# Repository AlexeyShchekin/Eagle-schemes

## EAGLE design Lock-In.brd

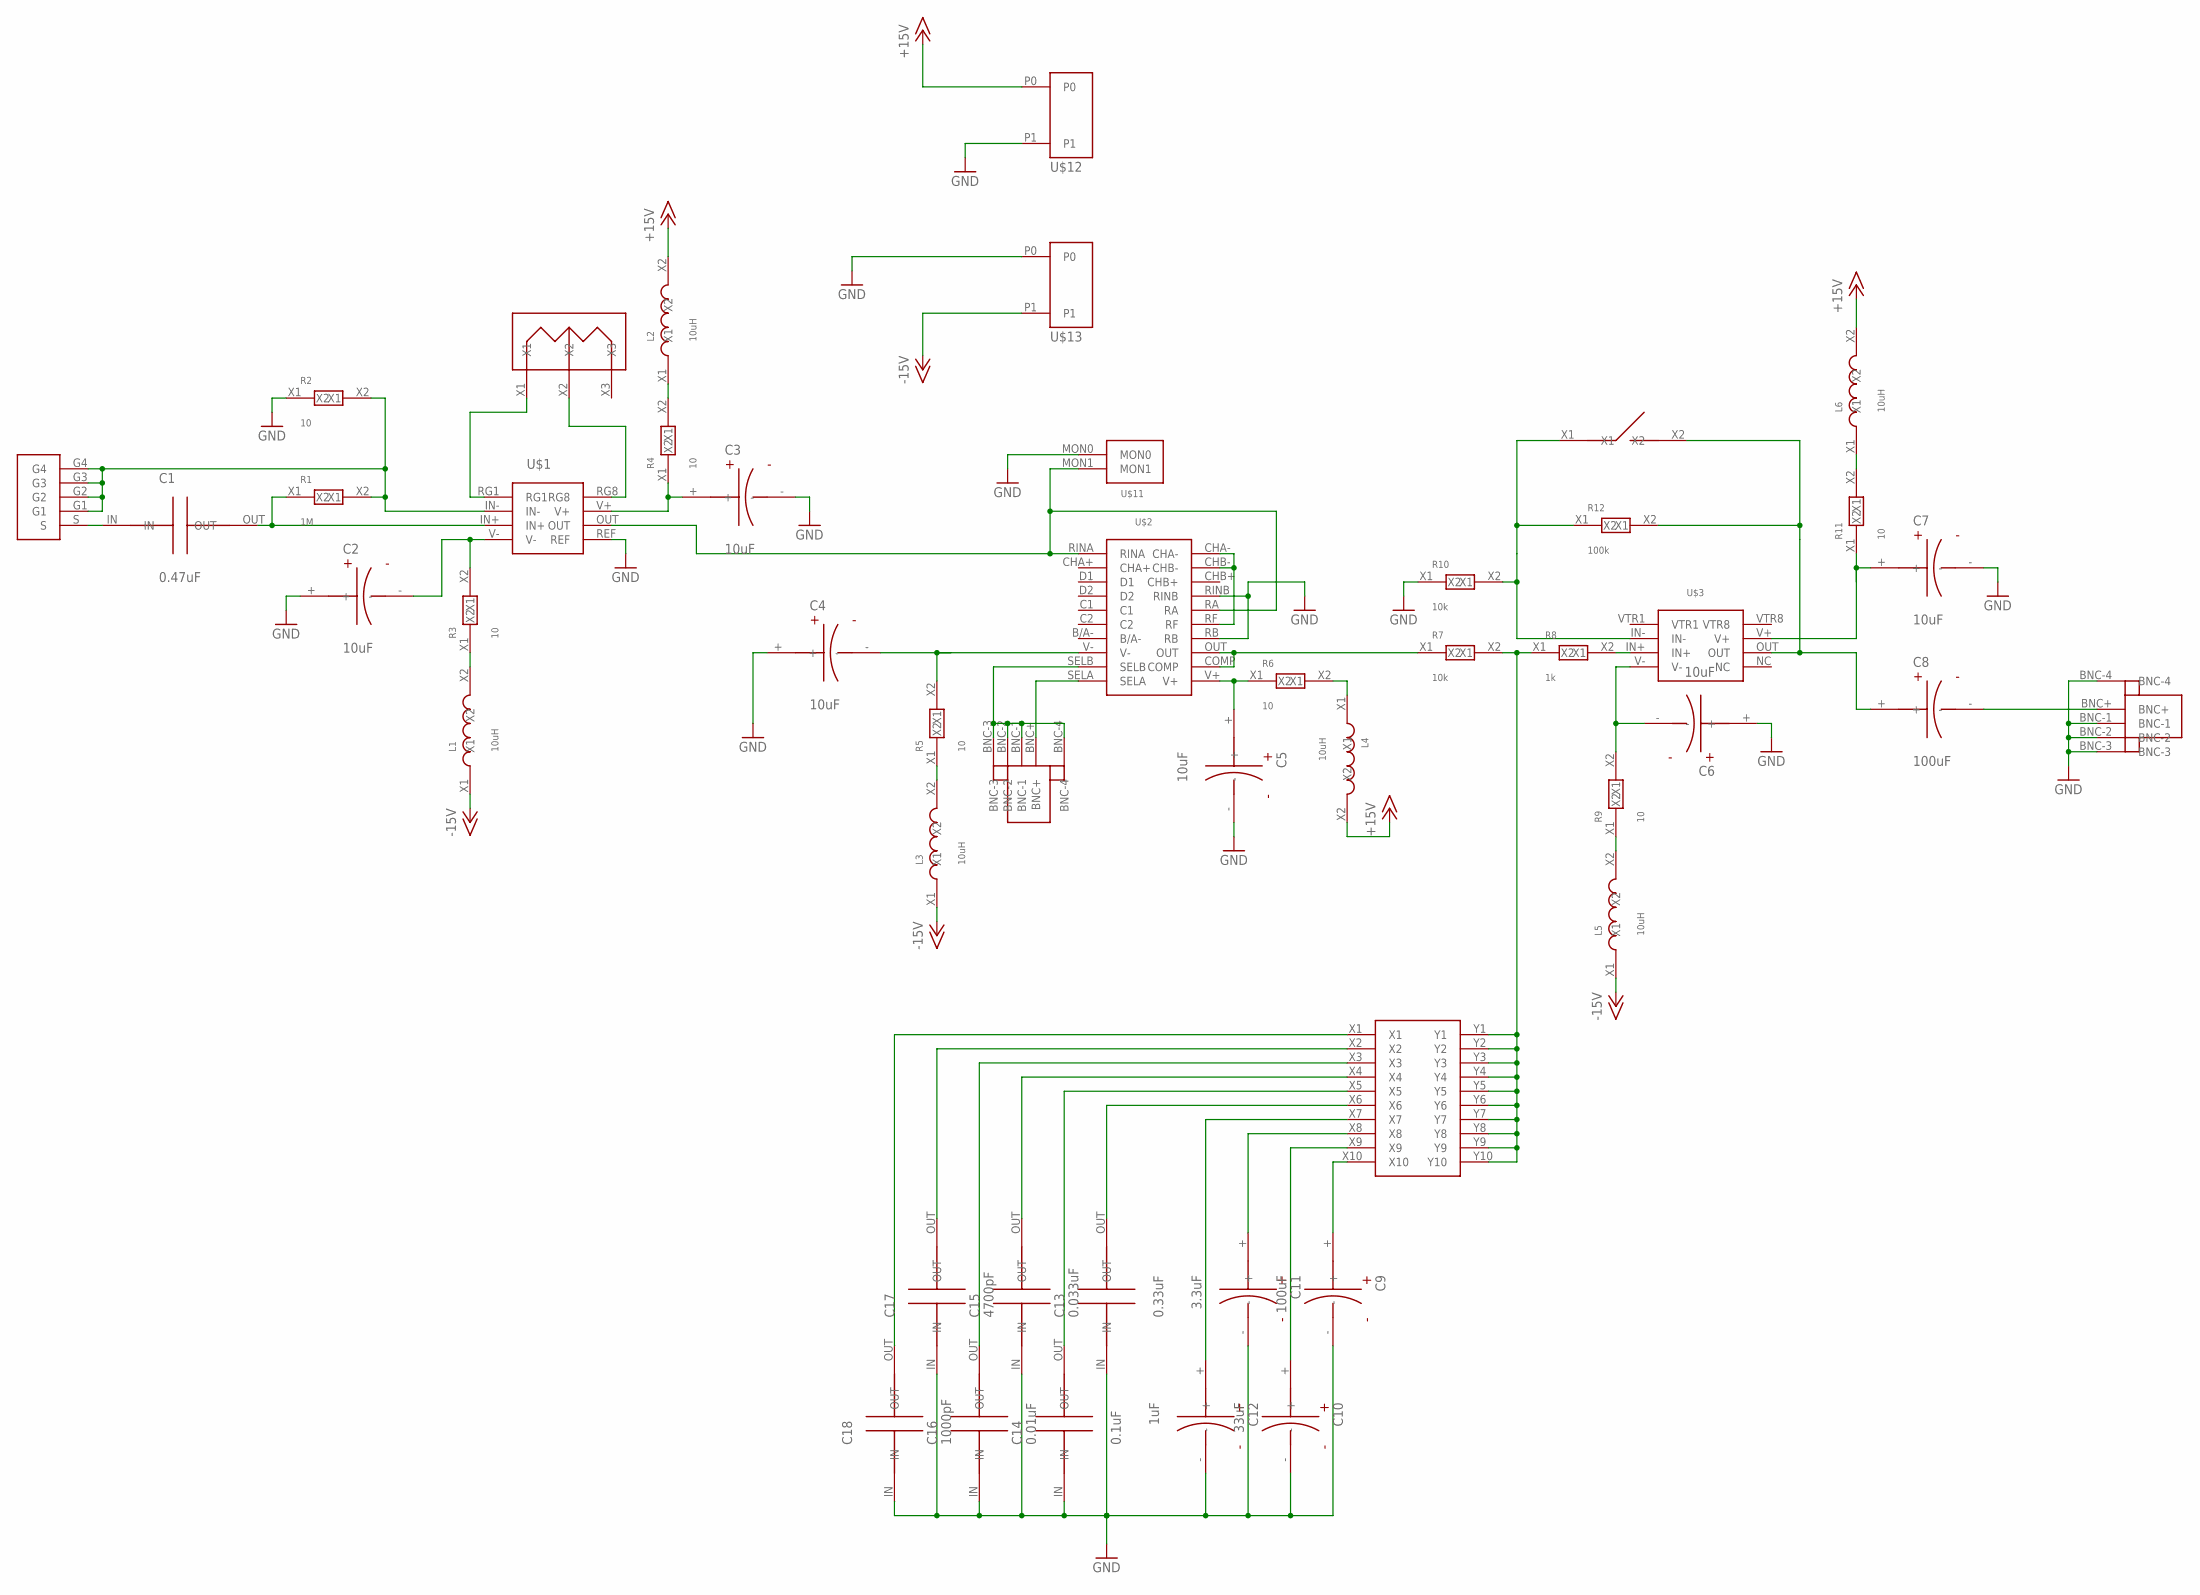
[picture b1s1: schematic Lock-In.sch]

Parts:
C1: 0.47uF; C_CER_5MM
C2, C3, C4, C5, C6, C7: 10uF; C_ELT_2MM
C8, C9: 100uF; C_ELT_2MM
C10: 33uF; C_ELT_2MM
C11: 3.3uF; C_ELT_2MM
C12: 1uF; C_ELT_2MM
C13: 0.33uF; C_CER_5MM
C14: 0.1uF; C_CER_5MM
C15: 0.033uF; C_CER_5MM
C16: 0.01uF; C_CER_5MM
C17: 4700pF; C_CER_5MM
C18: 1000pF; C_CER_5MM
L1, L2, L3, L4, L5, L6: 10uH; L_10X3
R1: 1M; R_6X2
R2, R3, R4, R5, R6, R9, R11: 10; R_6X2
R7, R10: 10k; R_6X2
R8: 1k; R_6X2
R12: 100k; R_6X2
U$1: AD620N
U$2: AD630
U$3: OP27
U$4, U$5: BNC
U$6: DIP10
U$7: R_VAR_10K
U$8: SMA_AN
U$9: DIP_1
U$11: MON2PIN
U$12, U$13: RAIL_2

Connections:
+15V: L2.X2, L4.X2, L6.X2, U$12.P0
-15V: L1.X1, L3.X1, L5.X1, U$13.P1
GND: C2.+, C3.-, C4.+, C5.-, C6.+, C7.-, C9.-, C10.-, C11.-, C12.-, C13.IN, C14.IN, C15.IN, C16.IN, C17.IN, C18.IN, R2.X1, R10.X1, U$1.REF, U$2.RB, U$2.RINB, U$5.BNC-1, U$5.BNC-2, U$5.BNC-3, U$5.BNC-4, U$11.MON0, U$12.P1, U$13.P0
unnamed: C1.IN, U$8.S
unnamed: R1.X2, R2.X2, U$1.IN-, U$8.G1, U$8.G2, U$8.G3, U$8.G4
unnamed: C1.OUT, R1.X1, U$1.IN+
unnamed: L1.X2, R3.X1
unnamed: C2.-, R3.X2, U$1.V-
unnamed: C3.+, R4.X1, U$1.V+
unnamed: U$1.RG1, U$7.X1
unnamed: U$1.RG8, U$7.X2
unnamed: L2.X1, R4.X2
unnamed: U$1.OUT, U$2.RA, U$2.RINA, U$11.MON1
unnamed: R7.X1, U$2.COMP, U$2.OUT
unnamed: U$2.CHA-, U$2.CHB-, U$2.RF
unnamed: U$2.SELA, U$4.BNC+
unnamed: U$2.SELB, U$4.BNC-1, U$4.BNC-2, U$4.BNC-3, U$4.BNC-4
unnamed: C5.+, R6.X1, U$2.V+
unnamed: L4.X1, R6.X2
unnamed: L3.X2, R5.X1
unnamed: C4.-, R5.X2, U$2.V-
unnamed: R7.X2, R8.X1, U$6.Y1, U$6.Y2, U$6.Y3, U$6.Y4, U$6.Y5, U$6.Y6, U$6.Y7, U$6.Y8, U$6.Y9, U$6.Y10
unnamed: R8.X2, U$3.IN+
unnamed: L5.X2, R9.X1
unnamed: C6.-, R9.X2, U$3.V-
unnamed: R10.X2, R12.X1, U$3.IN-, U$9.X1
unnamed: C7.+, R11.X1, U$3.V+
unnamed: L6.X1, R11.X2
unnamed: C8.+, R12.X2, U$3.OUT, U$9.X2
unnamed: C8.-, U$5.BNC+
unnamed: C9.+, U$6.X10
unnamed: C10.+, U$6.X9
unnamed: C11.+, U$6.X8
unnamed: C12.+, U$6.X7
unnamed: C13.OUT, U$6.X6
unnamed: C14.OUT, U$6.X5
unnamed: C15.OUT, U$6.X4
unnamed: C16.OUT, U$6.X3
unnamed: C17.OUT, U$6.X2
unnamed: C18.OUT, U$6.X1

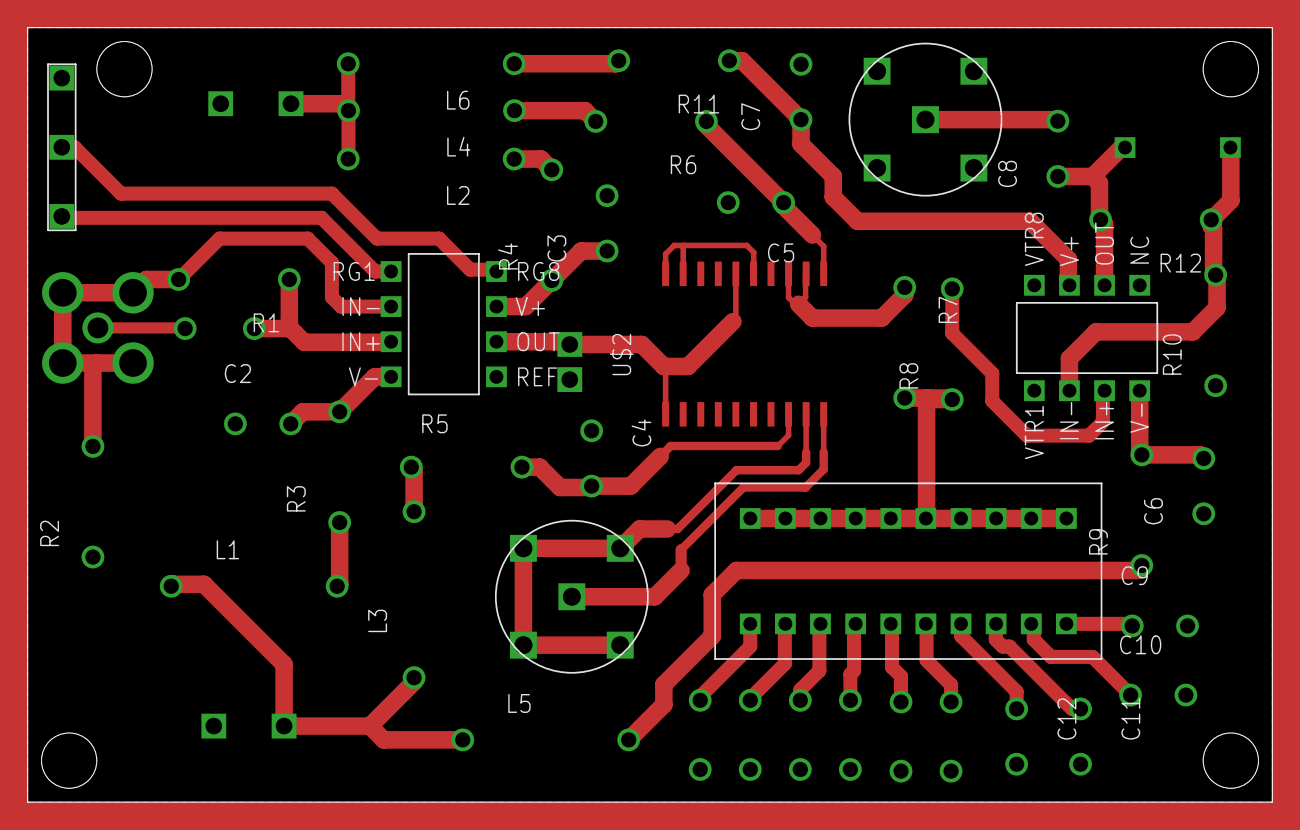
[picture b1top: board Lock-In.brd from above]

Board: 2 copper layers, 90.0 x 56.0 mm, 48 parts (0 on the bottom side), 40 nets.

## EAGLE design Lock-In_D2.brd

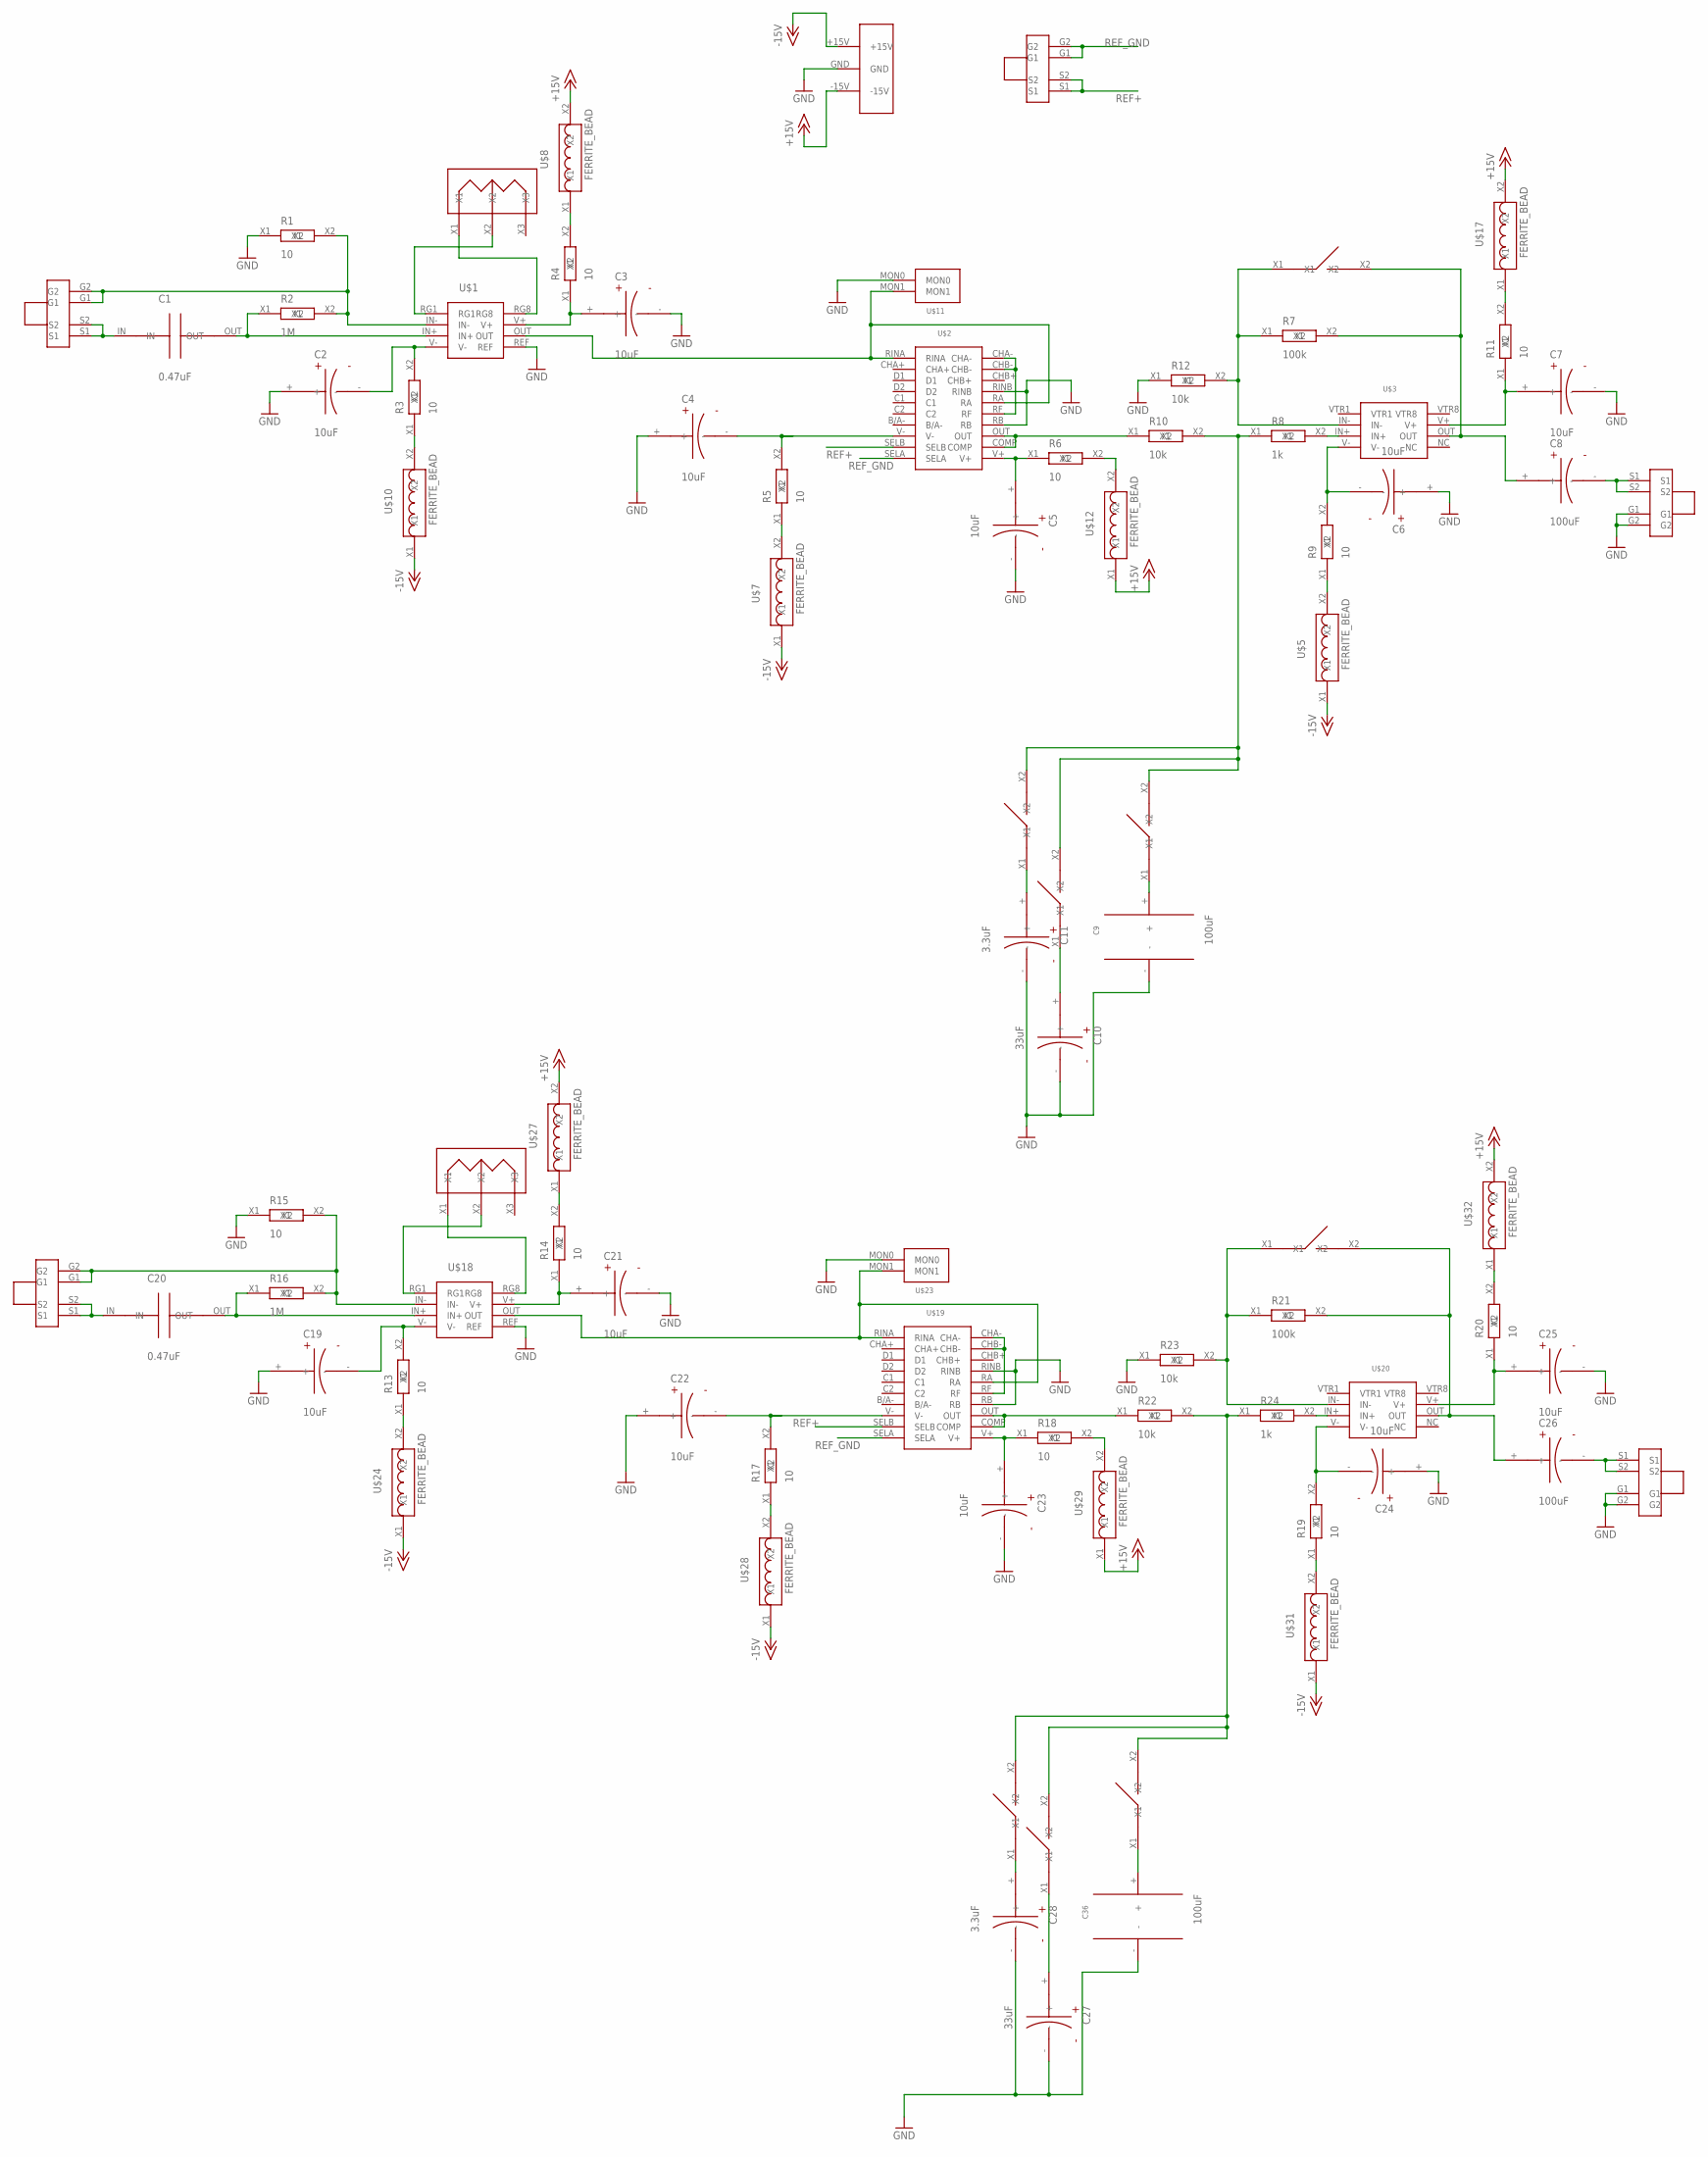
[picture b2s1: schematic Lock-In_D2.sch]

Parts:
C1, C20: 0.47uF; C_CER_5MM
C2, C3, C4, C5, C6, C7, C19, C21, C22, C23, C24, C25: 10uF; C_ELT_2MM
C8, C26: 100uF; C_ELT_2MM
C9, C36: 100uF; C100UF
C10, C27: 33uF; C_ELT_2MM
C11, C28: 3.3uF; C_ELT_2MM
R1, R3, R4, R5, R6, R9, R11, R13, R14, R15, R17, R18, R19, R20: 10; SMD_2.1X1.25
R2, R16: 1M; SMD_2.1X1.25
R7, R21: 100k; SMD_2.1X1.25
R8, R24: 1k; SMD_2.1X1.25
R10, R12, R22, R23: 10k; SMD_2.1X1.25
U$1, U$18: AD620N
U$2, U$19: AD630
U$3, U$20: OP27
U$4, U$13, U$16, U$26, U$30: BNC_A
U$5, U$7, U$8, U$10, U$12, U$17, U$24, U$27, U$28, U$29, U$31, U$32: FERRITE_BEAD
U$6, U$9, U$21, U$22, U$33, U$34, U$35, U$36: DIP_1
U$11, U$23: MON2PIN
U$14, U$25: R_VAR_3296W-1-103LF
U$15: SUPPLY

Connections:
+15V: U$8.X2, U$12.X1, U$15.-15V, U$17.X2, U$27.X2, U$29.X1, U$32.X2
-15V: U$5.X1, U$7.X1, U$10.X1, U$15.+15V, U$24.X1, U$28.X1, U$31.X1
GND: C2.+, C3.-, C4.+, C5.-, C6.+, C7.-, C9.-, C10.-, C11.-, C19.+, C21.-, C22.+, C23.-, C24.+, C25.-, C27.-, C28.-, C36.-, R1.X1, R12.X1, R15.X1, R23.X1, U$1.REF, U$2.RB, U$2.RINB, U$4.G1, U$4.G2, U$11.MON0, U$15.GND, U$18.REF, U$19.RB, U$19.RINB, U$23.MON0, U$30.G1, U$30.G2
unnamed: C1.IN, U$16.S1, U$16.S2
unnamed: R1.X2, R2.X2, U$1.IN-, U$16.G1, U$16.G2
unnamed: C1.OUT, R2.X1, U$1.IN+
unnamed: R3.X1, U$10.X2
unnamed: R4.X2, U$8.X1
unnamed: C2.-, R3.X2, U$1.V-
unnamed: C3.+, R4.X1, U$1.V+
unnamed: U$1.RG1, U$14.X2
unnamed: U$1.RG8, U$14.X1
unnamed: R5.X1, U$7.X2
unnamed: U$1.OUT, U$2.RA, U$2.RINA, U$11.MON1
unnamed: R10.X1, U$2.COMP, U$2.OUT
unnamed: U$2.CHA-, U$2.CHB-, U$2.RF
unnamed: C20.IN, U$26.S1, U$26.S2
unnamed: R15.X2, R16.X2, U$18.IN-, U$26.G1, U$26.G2
unnamed: C5.+, R6.X1, U$2.V+
unnamed: R6.X2, U$12.X2
unnamed: C8.-, U$4.S1, U$4.S2
unnamed: C4.-, R5.X2, U$2.V-
unnamed: R8.X1, R10.X2, U$34.X2, U$35.X2, U$36.X2
unnamed: R8.X2, U$3.IN+
unnamed: R9.X1, U$5.X2
unnamed: C6.-, R9.X2, U$3.V-
unnamed: R7.X1, R12.X2, U$3.IN-, U$9.X1
unnamed: C7.+, R11.X1, U$3.V+
unnamed: R11.X2, U$17.X1
unnamed: C8.+, R7.X2, U$3.OUT, U$9.X2
unnamed: C20.OUT, R16.X1, U$18.IN+
unnamed: C9.+, U$36.X1
unnamed: C10.+, U$35.X1
unnamed: C19.-, R13.X2, U$18.V-
unnamed: C11.+, U$34.X1
unnamed: U$18.RG1, U$25.X2
unnamed: U$18.RG8, U$25.X1
unnamed: C21.+, R14.X1, U$18.V+
unnamed: U$18.OUT, U$19.RA, U$19.RINA, U$23.MON1
unnamed: U$19.CHA-, U$19.CHB-, U$19.RF
unnamed: R22.X1, U$19.COMP, U$19.OUT
unnamed: C22.-, R17.X2, U$19.V-
unnamed: C23.+, R18.X1, U$19.V+
unnamed: R22.X2, R24.X1, U$6.X2, U$21.X2, U$33.X2
unnamed: C24.-, R19.X2, U$20.V-
unnamed: R21.X1, R23.X2, U$20.IN-, U$22.X1
unnamed: C25.+, R20.X1, U$20.V+
unnamed: C26.+, R21.X2, U$20.OUT, U$22.X2
unnamed: C36.+, U$6.X1
unnamed: C27.+, U$33.X1
unnamed: C28.+, U$21.X1
unnamed: R13.X1, U$24.X2
unnamed: R14.X2, U$27.X1
unnamed: R17.X1, U$28.X2
unnamed: R18.X2, U$29.X2
unnamed: C26.-, U$30.S1, U$30.S2
unnamed: R19.X1, U$31.X2
unnamed: R20.X2, U$32.X1
unnamed: R24.X2, U$20.IN+
REF+: U$2.SELB, U$13.S1, U$13.S2, U$19.SELB
REF_GND: U$2.SELA, U$13.G1, U$13.G2, U$19.SELA

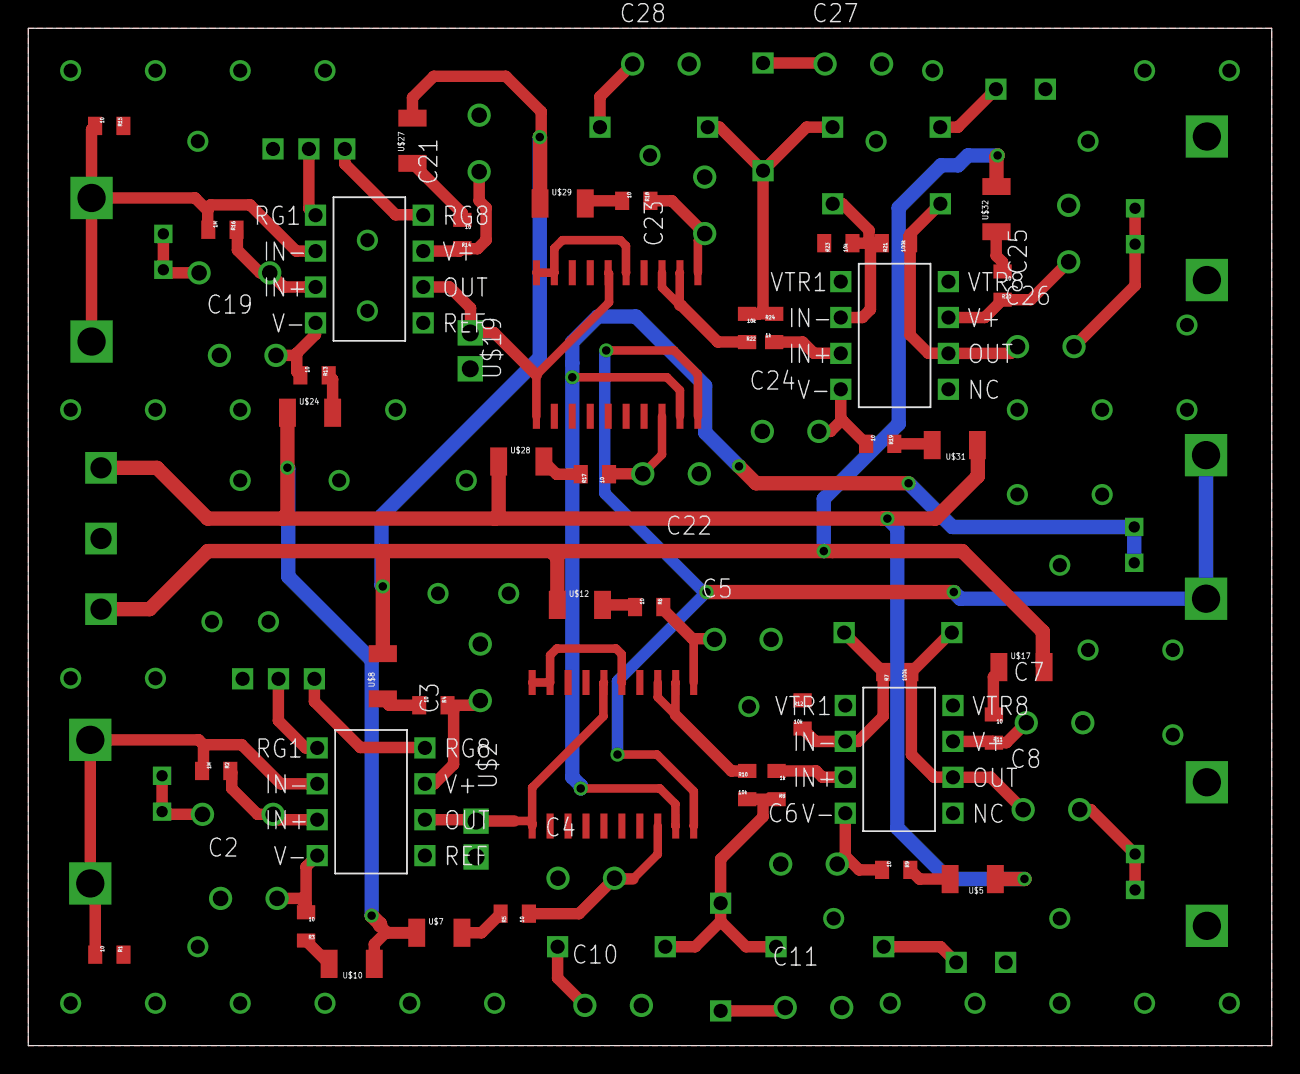
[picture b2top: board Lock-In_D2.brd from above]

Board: 2 copper layers, 88.0 x 72.0 mm, 82 parts (0 on the bottom side), 61 nets.

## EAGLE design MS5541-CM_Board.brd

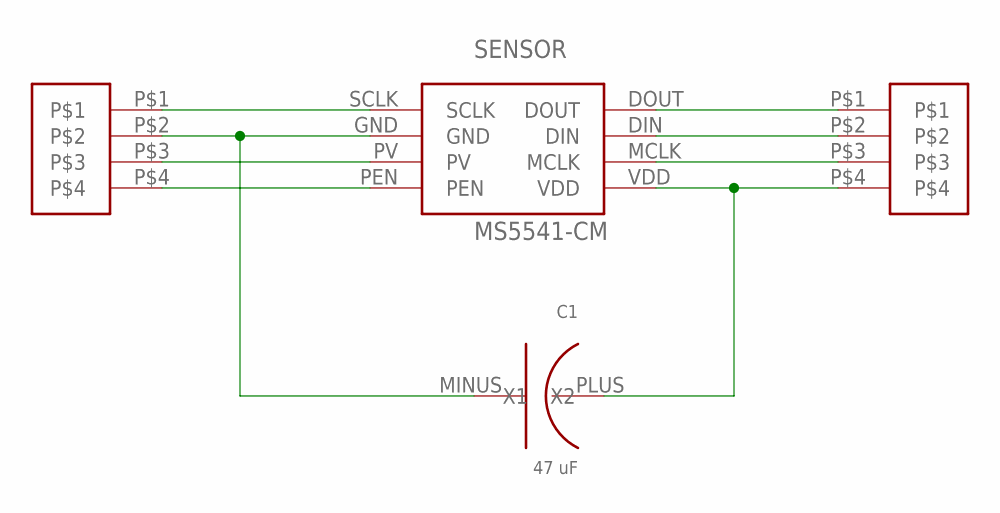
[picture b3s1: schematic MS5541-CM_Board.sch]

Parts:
C1: 47 uF; C_SMD_TA_B_BOTTOM
SENSOR: MS5541-CM
U$3, U$4: 4-PIN-NONAME

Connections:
unnamed: SENSOR.SCLK, U$4.P$1
unnamed: C1.MINUS (X2), SENSOR.GND, U$4.P$2
unnamed: SENSOR.PV, U$4.P$3
unnamed: SENSOR.PEN, U$4.P$4
unnamed: SENSOR.DOUT, U$3.P$1
unnamed: SENSOR.DIN, U$3.P$2
unnamed: SENSOR.MCLK, U$3.P$3
unnamed: C1.PLUS (X1), SENSOR.VDD, U$3.P$4

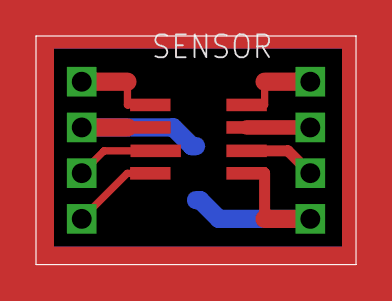
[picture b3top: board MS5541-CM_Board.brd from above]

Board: 2 copper layers, 17.8 x 12.7 mm, 4 parts (0 on the bottom side), 8 nets.

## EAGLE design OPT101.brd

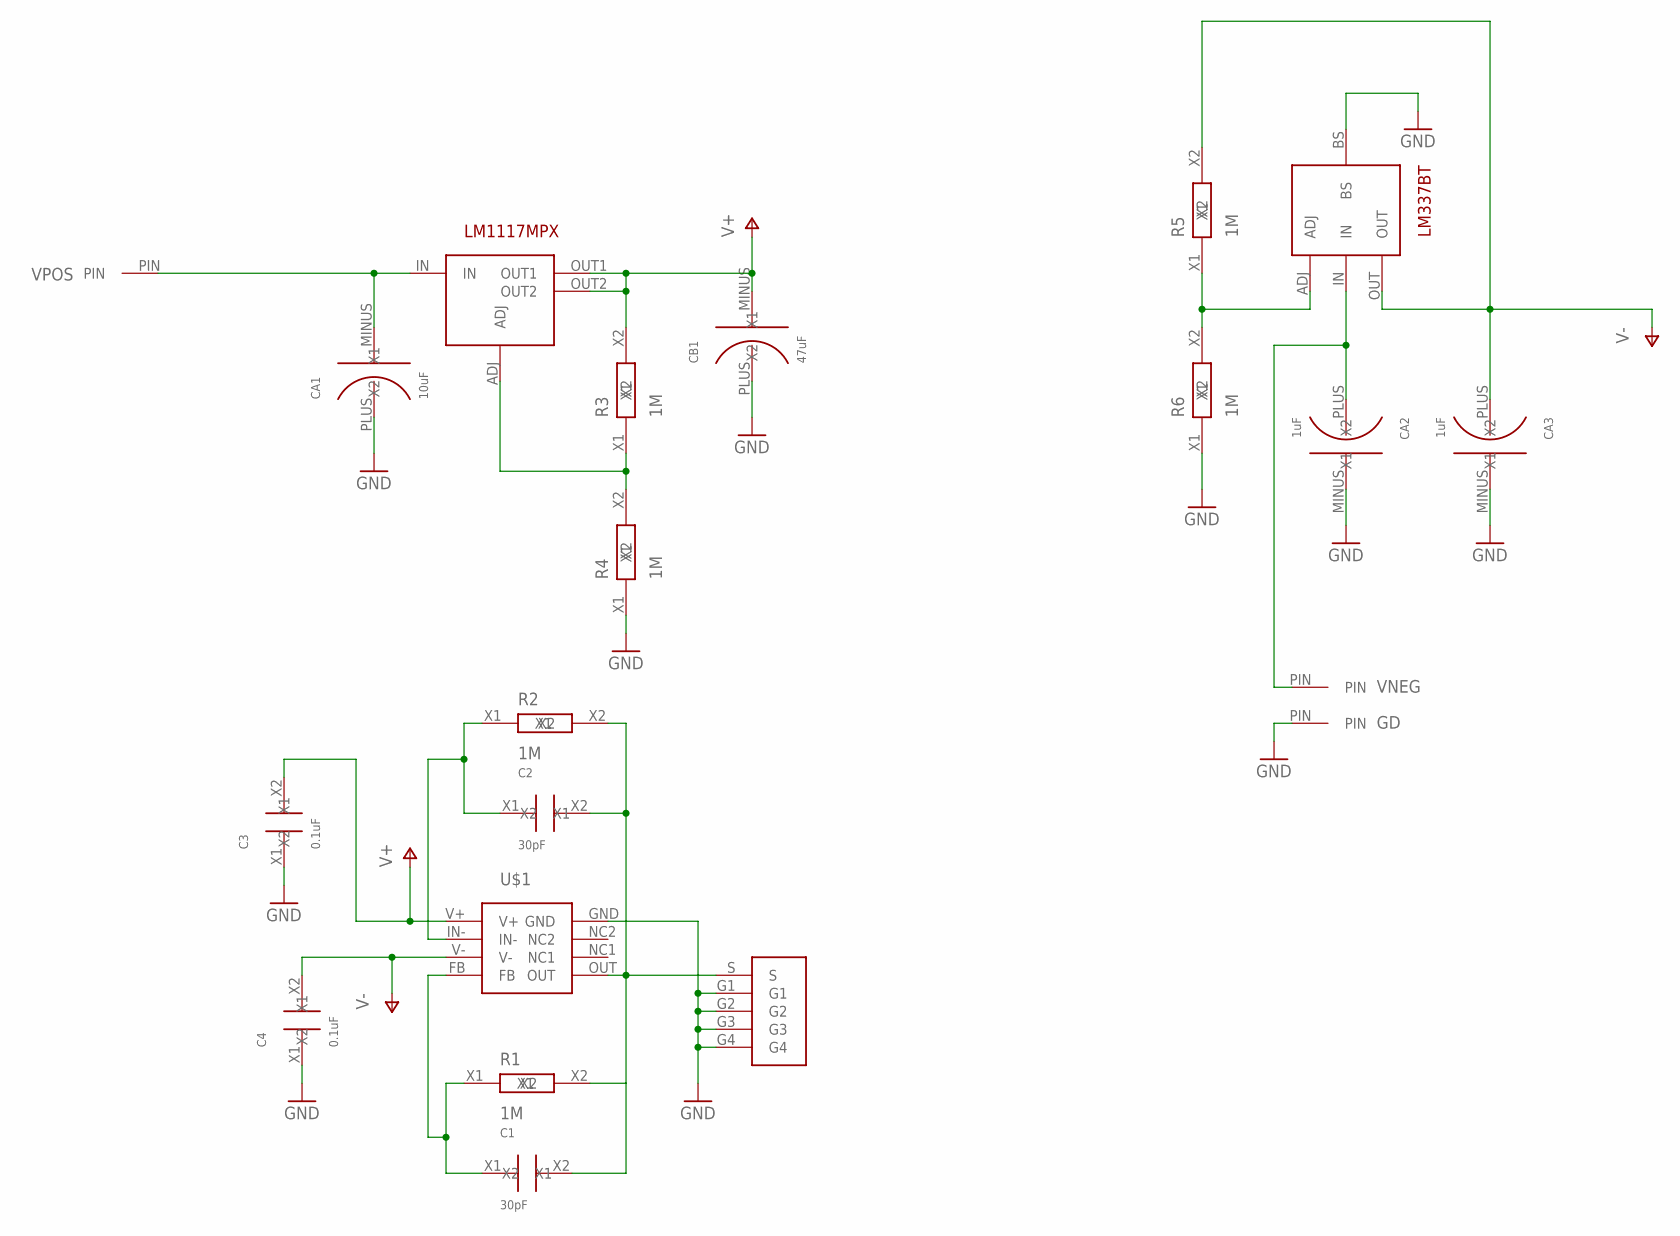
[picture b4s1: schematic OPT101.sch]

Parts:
C1, C2: 30pF; SMD_2.1X1.25
C3, C4: 0.1uF; SMD_2.1X1.25
CA1: 10uF; C_SMD_TA_A
CA2, CA3: 1uF; C_SMD_TA_A
CB1: 47uF; C_SMD_TA_B
GD: PIN
R1, R2, R3, R4, R5, R6: 1M; SMD_2.1X1.25
U$1: OPT101
U$2: SMA_AN
U$3: LM1117MPX-ADJ
U$4: LM337BT
VNEG: PIN
VPOS: PIN

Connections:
GND: C3.X1, C4.X1, CA1.PLUS (X1), CA2.MINUS (X2), CA3.MINUS (X2), CB1.PLUS (X1), GD.PIN, R4.X1, R6.X1, U$1.GND, U$2.G1, U$2.G2, U$2.G3, U$2.G4, U$4.BS
unnamed: C1.X2, C2.X2, R1.X2, R2.X2, U$1.OUT, U$2.S
unnamed: C2.X1, R2.X1, U$1.IN-
unnamed: C1.X1, R1.X1, U$1.FB
unnamed: CA1.MINUS (X2), U$3.IN, VPOS.PIN
unnamed: R3.X1, R4.X2, U$3.ADJ
unnamed: CA2.PLUS (X1), U$4.IN, VNEG.PIN
unnamed: R5.X1, R6.X2, U$4.ADJ
V+: C3.X2, CB1.MINUS (X2), R3.X2, U$1.V+, U$3.OUT1, U$3.OUT2
V-: C4.X2, CA3.PLUS (X1), R5.X2, U$1.V-, U$4.OUT

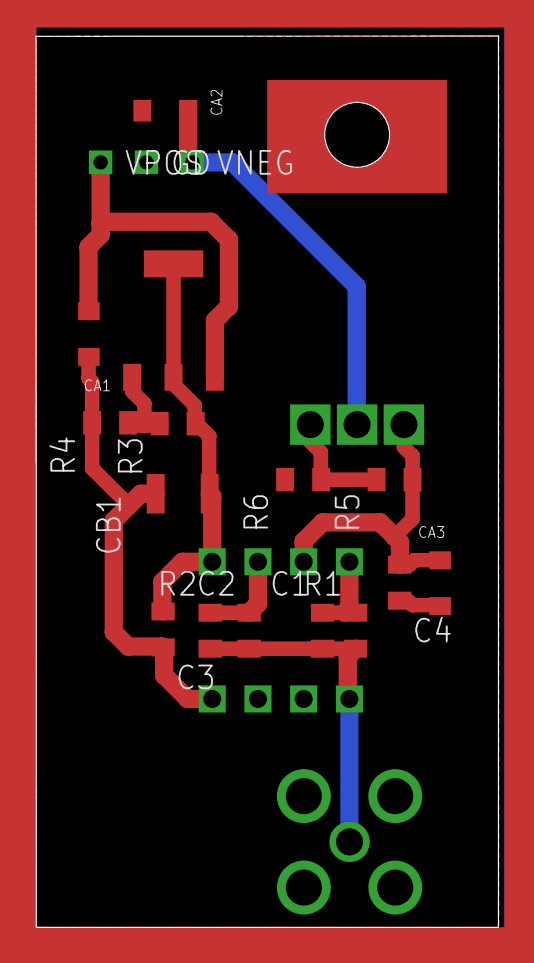
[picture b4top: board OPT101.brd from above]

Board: 2 copper layers, 25.7 x 49.5 mm, 21 parts (1 on the bottom side), 10 nets.

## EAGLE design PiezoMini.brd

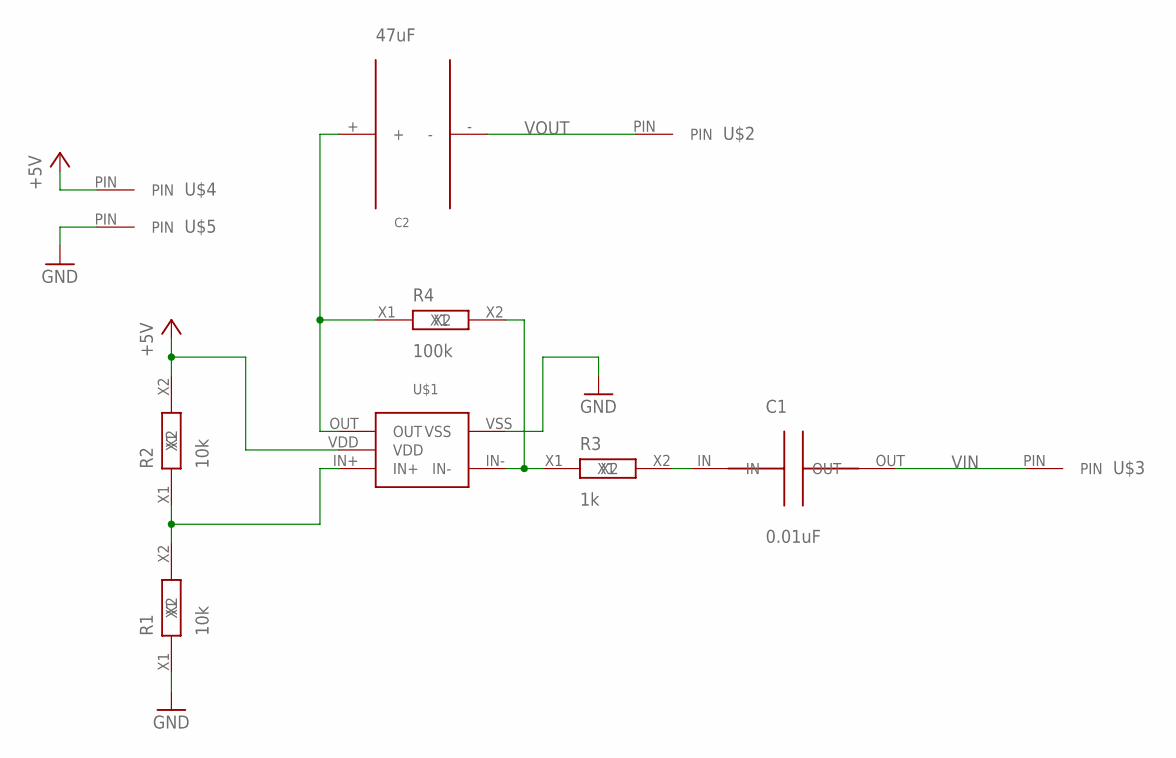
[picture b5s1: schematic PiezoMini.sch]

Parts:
C1: 0.01uF; C_CER_5MM
C2: 47uF; C100UF
R1, R2: 10k; SMD_2.1X1.25
R3: 1k; SMD_2.1X1.25
R4: 100k; SMD_2.1X1.25
U$1: MCP6L91
U$2, U$3, U$4, U$5: PIN

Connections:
+5V: R2.X2, U$1.VDD, U$4.PIN
GND: R1.X1, U$1.VSS, U$5.PIN
unnamed: R3.X1, R4.X2, U$1.IN-
unnamed: C1.IN, R3.X2
unnamed: C2.+, R4.X1, U$1.OUT
unnamed: R1.X2, R2.X1, U$1.IN+
VIN: C1.OUT, U$3.PIN
VOUT: C2.-, U$2.PIN

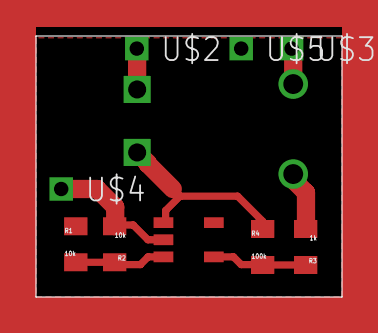
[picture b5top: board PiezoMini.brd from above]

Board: 2 copper layers, 17.0 x 14.5 mm, 11 parts (0 on the bottom side), 8 nets.

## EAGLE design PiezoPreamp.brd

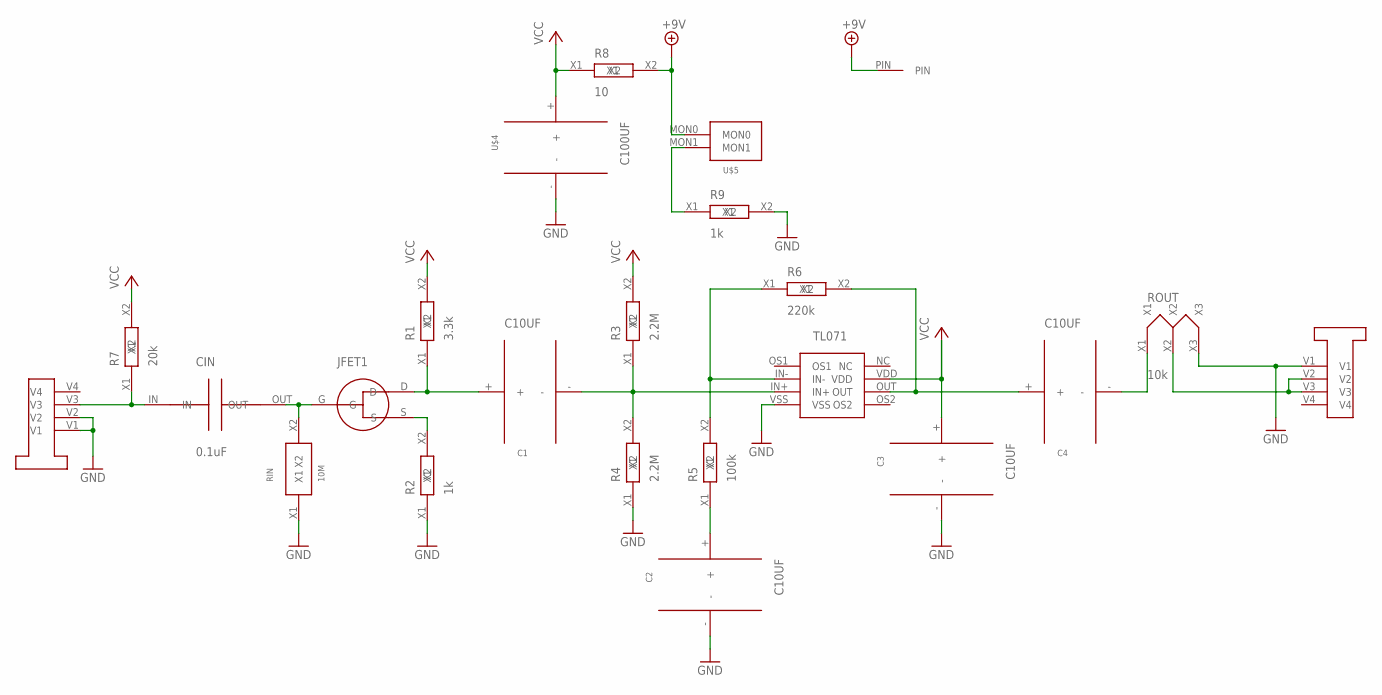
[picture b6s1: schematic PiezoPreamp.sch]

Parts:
C1, C2, C3, C4: C10UF
CIN: 0.1uF; C_CER_5MM
JFET1: 2N5457_H
R1: 3.3k; SMD_2.1X1.25
R2, R9: 1k; SMD_2.1X1.25
R3, R4: 2.2M; SMD_2.1X1.25
R5: 100k; SMD_2.1X1.25
R6: 220k; SMD_2.1X1.25
R7: 20k; SMD_2.1X1.25
R8: 10; SMD_2.1X1.25
RIN: 10M; R_MOM
ROUT: 10k; R_VAR_PTV09A
TL071: TL071
U$1, U$2: ST_AUDIO
U$3: PIN_1
U$4: C100UF
U$5: MON2PIN

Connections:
+9V: R8.X2, U$3.PIN, U$5.MON0
GND: C2.-, C3.-, R2.X1, R4.X1, R9.X2, RIN.X1, ROUT.X3, TL071.VSS, U$1.V1, U$1.V2, U$2.V1, U$4.-
unnamed: CIN.OUT, JFET1.G, RIN.X2
unnamed: C1.+, JFET1.D, R1.X1
unnamed: JFET1.S, R2.X2
unnamed: C1.-, R3.X1, R4.X2, TL071.IN+
unnamed: C2.+, R5.X1
unnamed: R5.X2, R6.X1, TL071.IN-
unnamed: C4.+, R6.X2, TL071.OUT
unnamed: CIN.IN, R7.X1, U$1.V3
unnamed: R9.X1, U$5.MON1
unnamed: ROUT.X2, U$2.V2, U$2.V3
unnamed: C4.-, ROUT.X1
VCC: C3.+, R1.X2, R3.X2, R7.X2, R8.X1, TL071.VDD, U$4.+

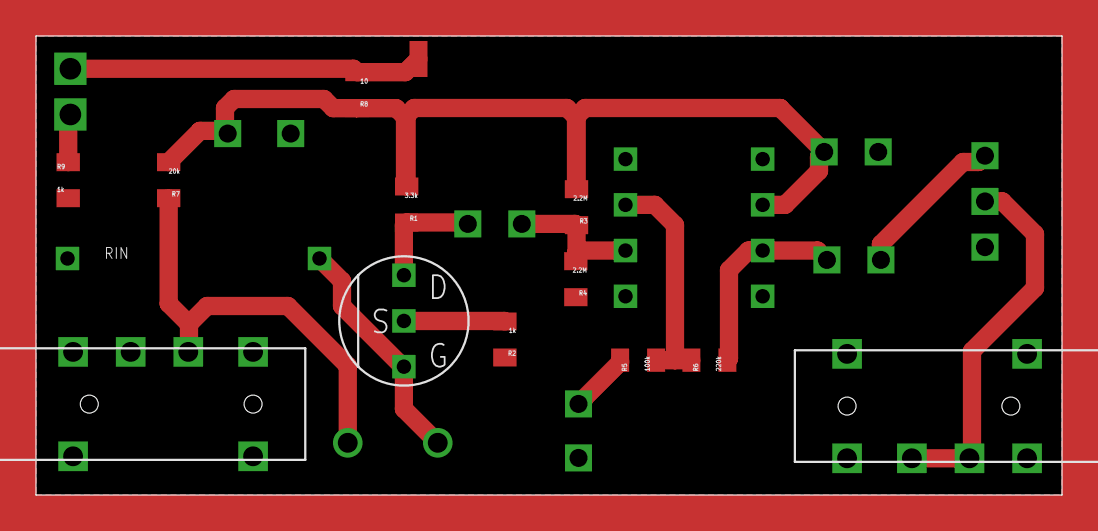
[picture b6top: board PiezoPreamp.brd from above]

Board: 2 copper layers, 57.0 x 25.5 mm, 23 parts (0 on the bottom side), 14 nets.

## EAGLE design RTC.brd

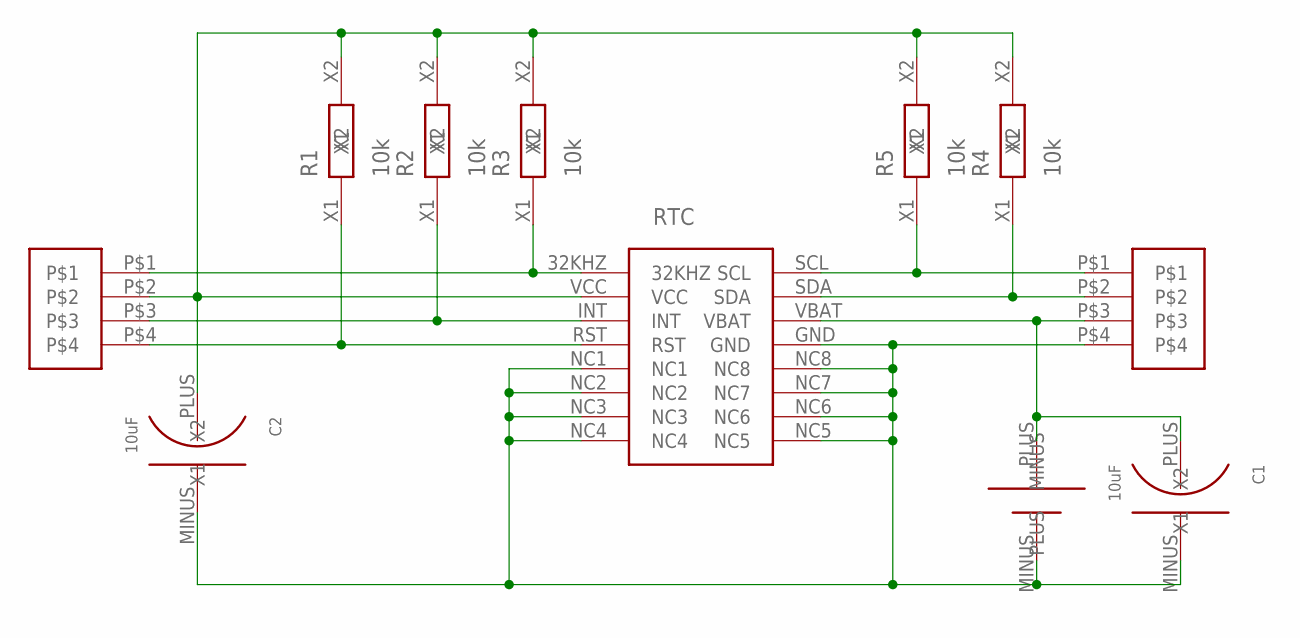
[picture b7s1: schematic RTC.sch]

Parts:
C1, C2: 10uF; C_SMD_TA_A
R1, R2, R3, R4, R5: 10k; SMD_2.1X1.25
RTC: RTC_DS3231
U$2: VBAT
U$3, U$4: 4-PIN-NONAME

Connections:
unnamed: R3.X1, RTC.32KHZ, U$4.P$1
unnamed: C2.PLUS (X1), R1.X2, R2.X2, R3.X2, R4.X2, R5.X2, RTC.VCC, U$4.P$2
unnamed: R2.X1, RTC.INT, U$4.P$3
unnamed: R1.X1, RTC.RST, U$4.P$4
unnamed: R5.X1, RTC.SCL, U$3.P$1
unnamed: R4.X1, RTC.SDA, U$3.P$2
unnamed: C1.PLUS (X1), RTC.VBAT, U$2.PLUS, U$3.P$3
unnamed: C1.MINUS (X2), C2.MINUS (X2), RTC.GND, RTC.NC1, RTC.NC2, RTC.NC3, RTC.NC4, RTC.NC5, RTC.NC6, RTC.NC7, RTC.NC8, U$2.MINUS, U$3.P$4

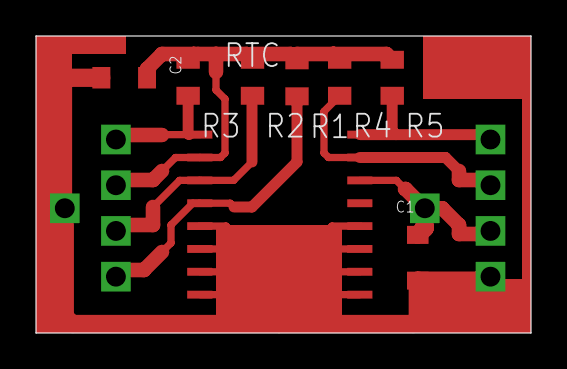
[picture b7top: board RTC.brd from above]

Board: 2 copper layers, 27.5 x 16.5 mm, 11 parts (0 on the bottom side), 8 nets.
